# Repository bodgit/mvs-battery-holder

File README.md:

MVS Battery Holder
==================

The original rechargeable battery on SNK Neo Geo MVS MV1B and MV1C boards should be replaced if it either doesn't hold a charge or before it leaks and destroys one or more vital PCB traces.

The original battery was either marked VG2430 or IVR2430 and the problem is that the solder legs use a spacing that no other battery or holder seems to have. Rather than hack something together here is a simple PCB that is spaced correctly and allows you to use most 3V 2032-sized coin cells.

For rechargeable coin cells, an LIR2032 seems a good choice as it outputs 3.6V and needs around 4V for charging which matches what the MVS charging circuit provides. An ML2032 only provides 3V and needs around 2.8-3.3V for charging so chances are the MVS charging circuit would damage the battery.

If you use a non-rechargeable CR2032 coin cell you must disable the charging circuit entirely on the MVS board otherwise this will damage the battery.

The BOM is simply a Keystone 3034 coin cell holder which should be easy to source. If you want to mount the PCB horizontally use three straight header pins, and if you want to mount the PCB vertically use three right-angled header pins.

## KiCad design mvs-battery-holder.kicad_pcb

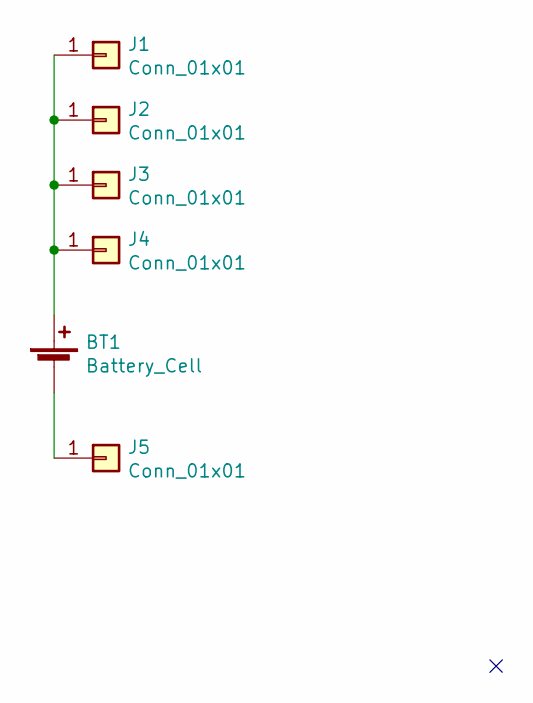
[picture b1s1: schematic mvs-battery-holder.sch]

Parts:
BT1: Battery_Cell; BatteryHolder_Keystone_3034_1x20mm
J1, J2, J5: Conn_01x01; PinHeader_1x01_P2.54mm_Horizontal
J3, J4: Conn_01x01; PinHeader_1x01_P2.54mm_Vertical

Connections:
unnamed: BT1.1 (+), J1.1, J2.1, J3.1, J4.1
unnamed: BT1.2 (-), J5.1

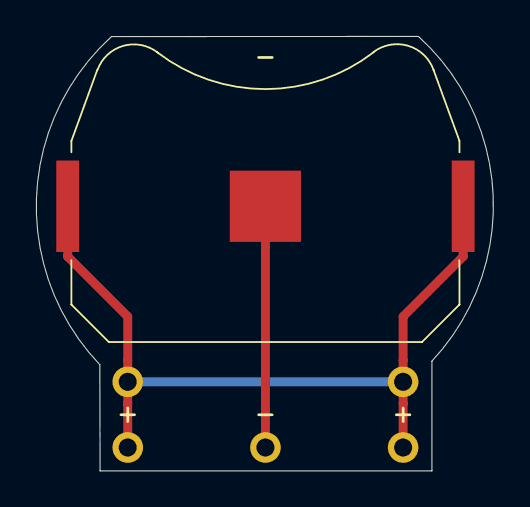
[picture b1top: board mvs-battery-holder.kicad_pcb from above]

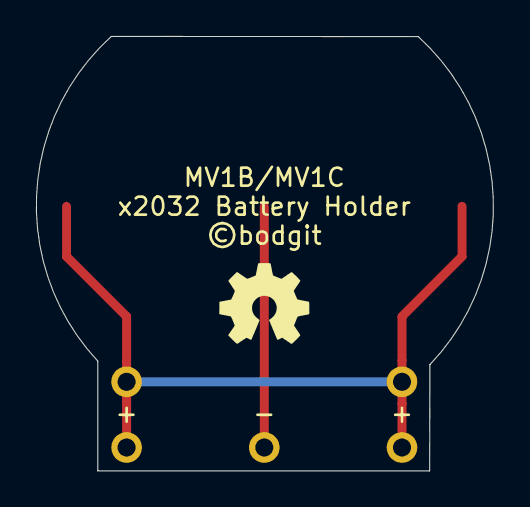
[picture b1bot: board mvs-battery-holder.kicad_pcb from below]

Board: 2 copper layers, 25.4 x 24.1 mm, 6 parts (4 on the bottom side), 2 nets.

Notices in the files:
mvs-battery-holder.kicad_pcb:
©bodgit
